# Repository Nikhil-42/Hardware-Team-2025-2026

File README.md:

# Hardware Team 2025-2026
This is the repository for the 2025-2026 IEEE Hardware Team SouthConn for UF.

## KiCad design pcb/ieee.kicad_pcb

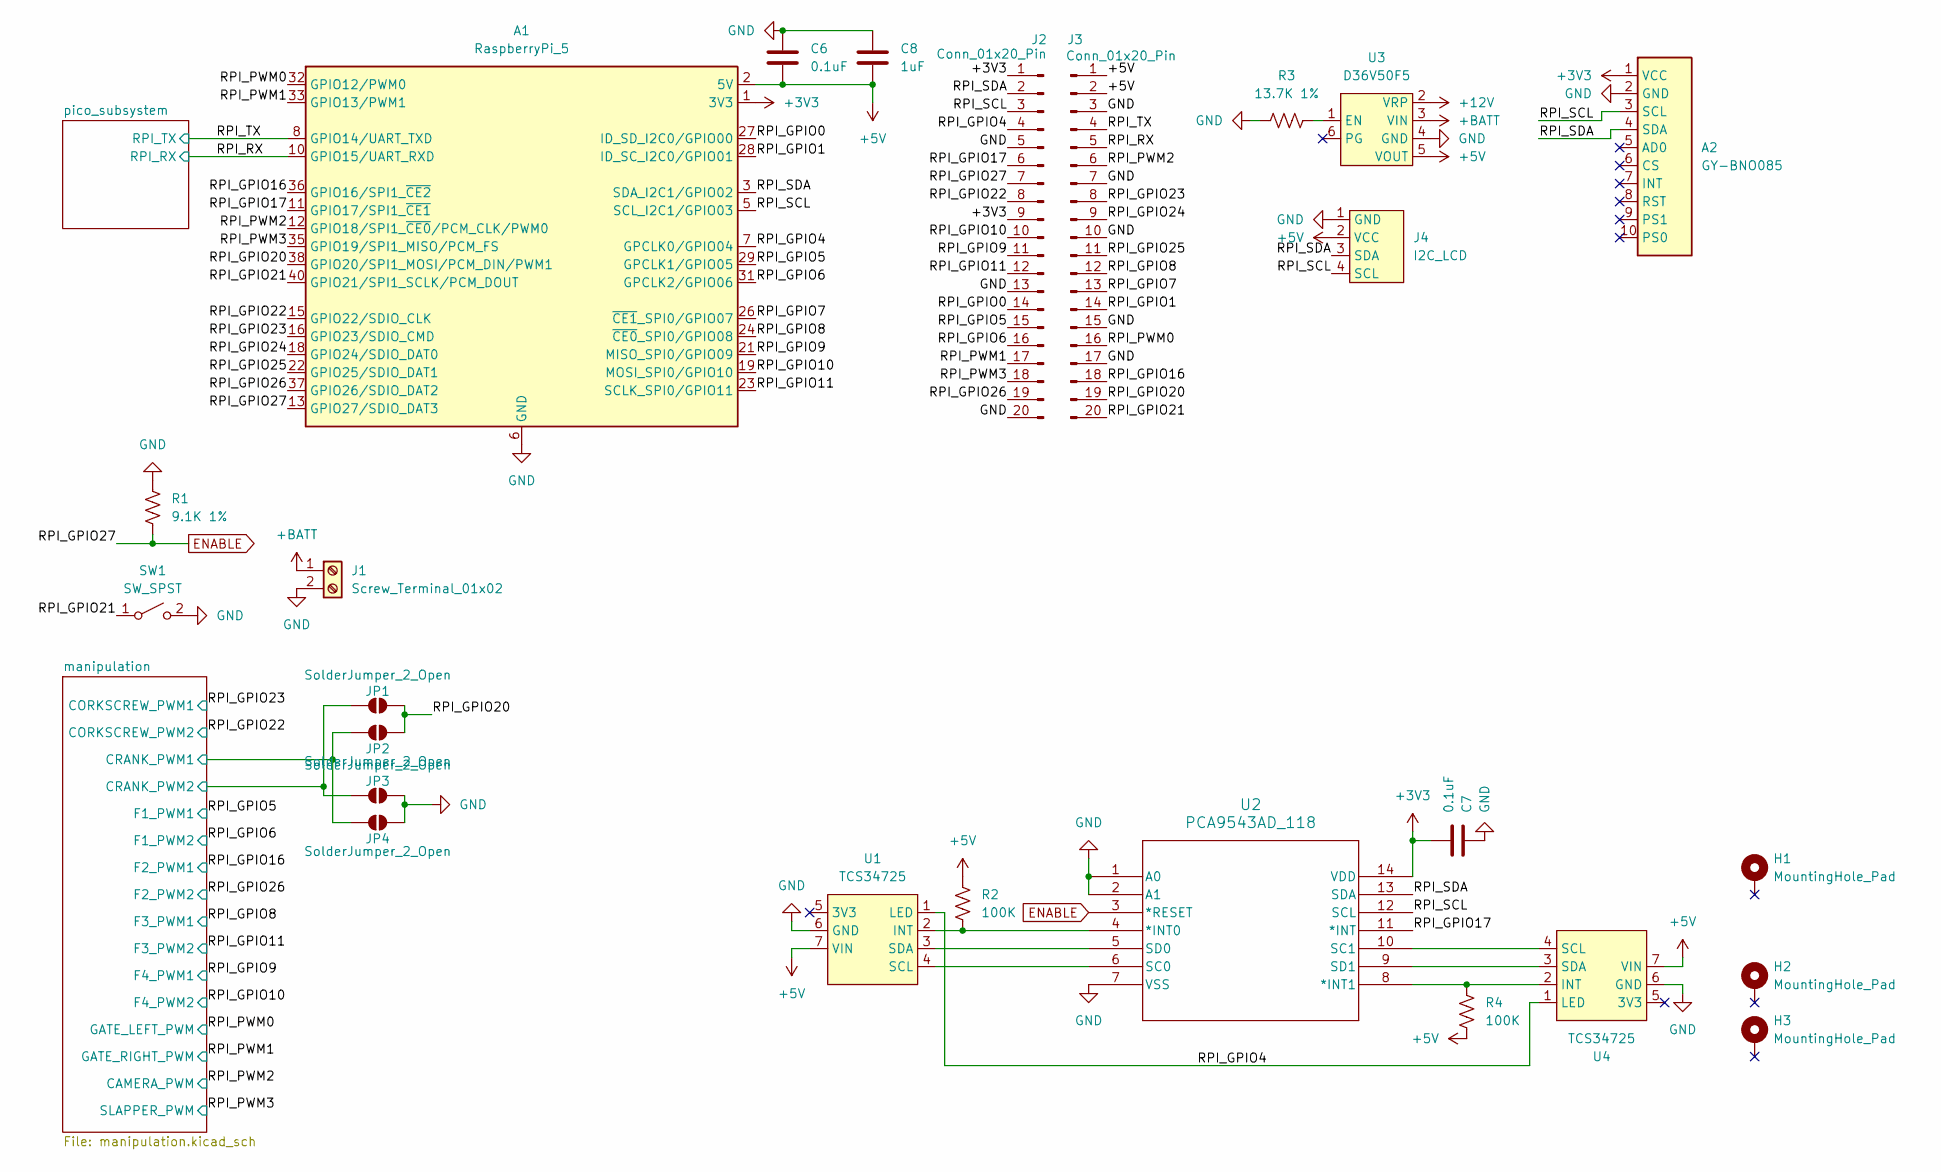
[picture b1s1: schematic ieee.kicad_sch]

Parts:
A1: RaspberryPi_5; Raspberry_Pi_5
A2: GY-BNO085
C6, C7: 0.1uF; C_0603_1608Metric_Pad1.08x0.95mm_HandSolder
C8: 1uF; C_0603_1608Metric_Pad1.08x0.95mm_HandSolder
H1, H2, H3: MountingHole_Pad; MountingHole_3.2mm_M3_Pad
J1: Screw_Terminal_01x02; TerminalBlock_MetzConnect_Type101_RT01602HBWC_1x02_P5.08mm_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
J2, J3: Conn_01x20_Pin; PinHeader_1x20_P2.54mm_Vertical
J4: I2C_LCD; PinHeader_1x04_P2.54mm_Vertical
JP1, JP2, JP3, JP4: SolderJumper_2_Open; SolderJumper-2_P1.3mm_Open_TrianglePad1.0x1.5mm
R1: 9.1K 1%; R_Axial_DIN0309_L9.0mm_D3.2mm_P15.24mm_Horizontal
R2, R4: 100K; R_Axial_DIN0309_L9.0mm_D3.2mm_P15.24mm_Horizontal
R3: 13.7K 1%; R_Axial_DIN0309_L9.0mm_D3.2mm_P15.24mm_Horizontal
SW1: SW_SPST; SW_PUSH_6mm
U1, U4: TCS34725; PinHeader_1x07_P2.54mm_Vertical
U2: PCA9543AD_118; SOIC-14_3.9x8.7mm_P1.27mm
U3: D36V50F5

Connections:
+3V3: A1.1 (3V3), A1.17 (3V3), A2.1 (VCC), C7.2, J2.1, J2.9, U2.14 (VDD)
+5V: A1.2 (5V), A1.4 (5V), C6.2, C8.2, J3.1, J3.2, J4.2 (VCC), R2.1, R4.2, U1.7 (VIN), U3.5 (VOUT), U4.7 (VIN); also elsewhere on the board
+12V: U3.2 (VRP)
+BATT: J1.1 (+), U3.3 (VIN); also elsewhere on the board
/RPI_GPIO0: A1.27 (ID_SD_I2C0/GPIO00), J2.14
/RPI_GPIO1: A1.28 (ID_SC_I2C0/GPIO01), J3.14
/RPI_GPIO4: A1.7 (GPCLK0/GPIO04), J2.4, U1.1 (LED), U4.1 (LED)
/RPI_GPIO5: A1.29 (GPCLK1/GPIO05), J2.15; also elsewhere on the board
/RPI_GPIO6: A1.31 (GPCLK2/GPIO06), J2.16; also elsewhere on the board
/RPI_GPIO7: A1.26 (~CE1_SPI0/GPIO07), J3.13
/RPI_GPIO8: A1.24 (~CE0_SPI0/GPIO08), J3.12; also elsewhere on the board
/RPI_GPIO9: A1.21 (MISO_SPI0/GPIO09), J2.11; also elsewhere on the board
/RPI_GPIO10: A1.19 (MOSI_SPI0/GPIO10), J2.10; also elsewhere on the board
/RPI_GPIO11: A1.23 (SCLK_SPI0/GPIO11), J2.12; also elsewhere on the board
/RPI_GPIO16: A1.36 (GPIO16/SPI1_~CE2), J3.18; also elsewhere on the board
/RPI_GPIO17: A1.11 (GPIO17/SPI1_~CE1), J2.6, U2.11 (*INT)
/RPI_GPIO20: A1.38 (GPIO20/SPI1_MOSI/PCM_DIN/PWM1), J3.19, JP1.2 (B), JP2.2 (B)
/RPI_GPIO21: A1.40 (GPIO21/SPI1_SCLK/PCM_DOUT), J3.20, SW1.1 (A)
/RPI_GPIO22: A1.15 (GPIO22/SDIO_CLK), J2.8; also elsewhere on the board
/RPI_GPIO23: A1.16 (GPIO23/SDIO_CMD), J3.8; also elsewhere on the board
/RPI_GPIO24: A1.18 (GPIO24/SDIO_DAT0), J3.9
/RPI_GPIO25: A1.22 (GPIO25/SDIO_DAT1), J3.11
/RPI_GPIO26: A1.37 (GPIO26/SDIO_DAT2), J2.19; also elsewhere on the board
/RPI_PWM0: A1.32 (GPIO12/PWM0), J3.16; also elsewhere on the board
/RPI_PWM1: A1.33 (GPIO13/PWM1), J2.17; also elsewhere on the board
/RPI_PWM2: A1.12 (GPIO18/SPI1_~CE0/PCM_CLK/PWM0), J3.6; also elsewhere on the board
/RPI_PWM3: A1.35 (GPIO19/SPI1_MISO/PCM_FS), J2.18; also elsewhere on the board
/RPI_RX: A1.10 (GPIO15/UART_RXD), J3.5; also elsewhere on the board
/RPI_SCL: A1.5 (SCL_I2C1/GPIO03), A2.3 (SCL), J2.3, J4.4 (SCL), U2.12 (SCL)
/RPI_SDA: A1.3 (SDA_I2C1/GPIO02), A2.4 (SDA), J2.2, J4.3 (SDA), U2.13 (SDA)
/RPI_TX: A1.8 (GPIO14/UART_TXD), J3.4; also elsewhere on the board
/manipulation/CRANK_PWM1: JP2.1 (A), JP4.1 (A); also elsewhere on the board
/manipulation/CRANK_PWM2: JP1.1 (A), JP3.1 (A); also elsewhere on the board
ENABLE: A1.13 (GPIO27/SDIO_DAT3), J2.7, R1.1, U2.3 (*RESET); also elsewhere on the board
GND: A1.6 (GND), A1.9 (GND), A1.14 (GND), A1.20 (GND), A1.25 (GND), A1.30 (GND), A1.34 (GND), A1.39 (GND), A2.2 (GND), C6.1, C7.1, C8.1, J1.2 (-), J2.5, J2.13, J2.20, J3.3, J3.7, J3.10, J3.15, J3.17, J4.1 (GND), JP3.2 (B), JP4.2 (B), R1.2, R3.1, SW1.2 (B), U1.6 (GND), U2.1 (A0), U2.2 (A1), U2.7 (VSS), U3.4 (GND), U4.6 (GND); also elsewhere on the board
unnamed: R2.2, U1.2 (INT), U2.4 (*INT0)
unnamed: U1.4 (SCL), U2.6 (SC0)
unnamed: U1.3 (SDA), U2.5 (SD0)
unnamed: R4.1, U2.8 (*INT1), U4.2 (INT)
unnamed: U2.10 (SC1), U4.4 (SCL)
unnamed: U2.9 (SD1), U4.3 (SDA)
unnamed: R3.2, U3.1 (EN)

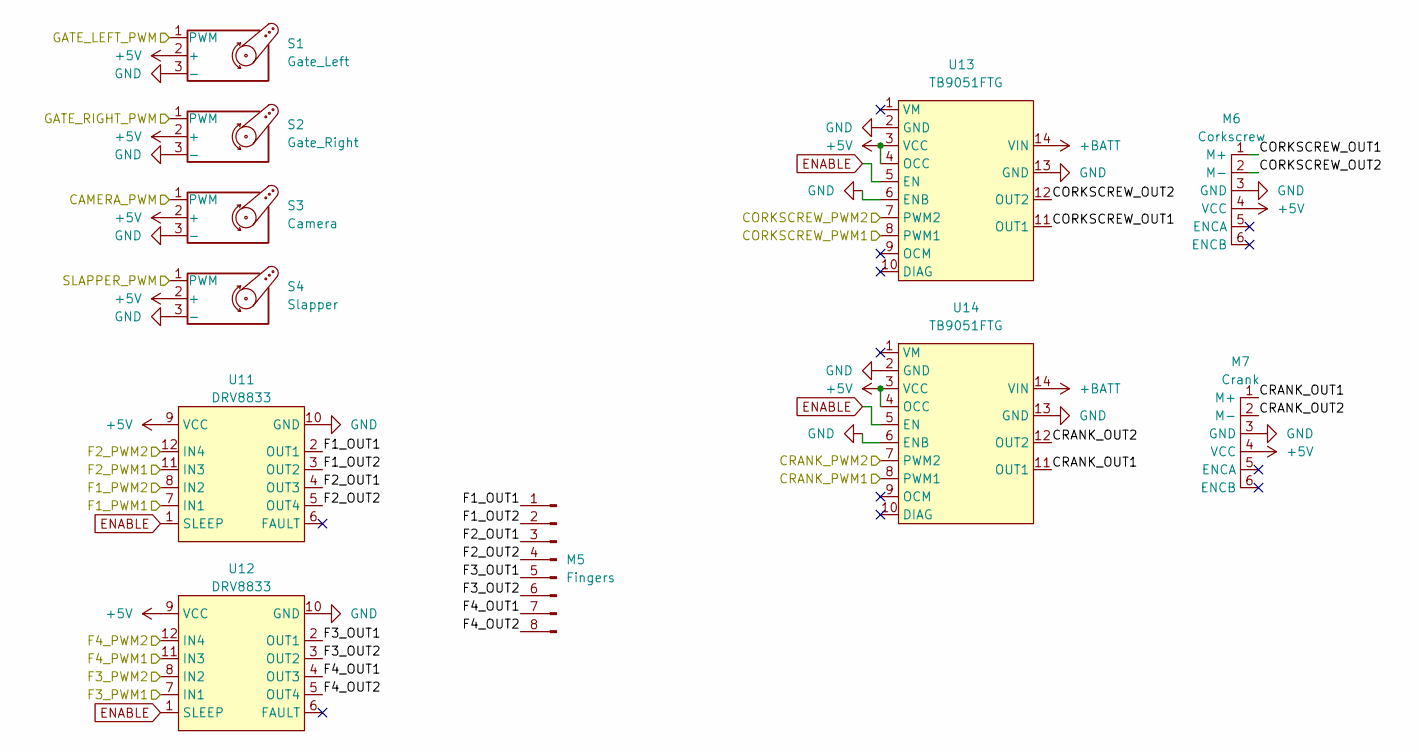
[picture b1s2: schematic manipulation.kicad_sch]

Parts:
M5: Fingers; PinHeader_1x08_P2.54mm_Vertical
M6: Corkscrew; PinHeader_1x06_P2.54mm_Vertical
M7: Crank; PinHeader_1x06_P2.54mm_Vertical
S1: Gate_Left; PinHeader_1x03_P2.54mm_Vertical
S2: Gate_Right; PinHeader_1x03_P2.54mm_Vertical
S3: Camera; PinHeader_1x03_P2.54mm_Vertical
S4: Slapper; PinHeader_1x03_P2.54mm_Vertical
U11, U12: DRV8833
U13, U14: TB9051FTG

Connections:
+5V: M6.4 (VCC), M7.4 (VCC), S1.2 (+), S2.2 (+), S3.2 (+), S4.2 (+), U11.9 (VCC), U12.9 (VCC), U13.3 (VCC), U13.4 (OCC), U14.3 (VCC), U14.4 (OCC); also elsewhere on the board
+BATT: U13.14 (VIN), U14.14 (VIN); also elsewhere on the board
/RPI_GPIO5: U11.7 (IN1); also elsewhere on the board
/RPI_GPIO6: U11.8 (IN2); also elsewhere on the board
/RPI_GPIO8: U12.7 (IN1); also elsewhere on the board
/RPI_GPIO9: U12.11 (IN3); also elsewhere on the board
/RPI_GPIO10: U12.12 (IN4); also elsewhere on the board
/RPI_GPIO11: U12.8 (IN2); also elsewhere on the board
/RPI_GPIO16: U11.11 (IN3); also elsewhere on the board
/RPI_GPIO22: U13.7 (PWM2); also elsewhere on the board
/RPI_GPIO23: U13.8 (PWM1); also elsewhere on the board
/RPI_GPIO26: U11.12 (IN4); also elsewhere on the board
/RPI_PWM0: S1.1 (PWM); also elsewhere on the board
/RPI_PWM1: S2.1 (PWM); also elsewhere on the board
/RPI_PWM2: S3.1 (PWM); also elsewhere on the board
/RPI_PWM3: S4.1 (PWM); also elsewhere on the board
/manipulation/CORKSCREW_OUT1: M6.1 (M+), U13.11 (OUT1)
/manipulation/CORKSCREW_OUT2: M6.2 (M-), U13.12 (OUT2)
/manipulation/CRANK_OUT1: M7.1 (M+), U14.11 (OUT1)
/manipulation/CRANK_OUT2: M7.2 (M-), U14.12 (OUT2)
/manipulation/CRANK_PWM1: U14.8 (PWM1); also elsewhere on the board
/manipulation/CRANK_PWM2: U14.7 (PWM2); also elsewhere on the board
/manipulation/F1_OUT1: M5.1, U11.2 (OUT1)
/manipulation/F1_OUT2: M5.2, U11.3 (OUT2)
/manipulation/F2_OUT1: M5.3, U11.4 (OUT3)
/manipulation/F2_OUT2: M5.4, U11.5 (OUT4)
/manipulation/F3_OUT1: M5.5, U12.2 (OUT1)
/manipulation/F3_OUT2: M5.6, U12.3 (OUT2)
/manipulation/F4_OUT1: M5.7, U12.4 (OUT3)
/manipulation/F4_OUT2: M5.8, U12.5 (OUT4)
ENABLE: U11.1 (SLEEP), U12.1 (SLEEP), U13.5 (EN), U14.5 (EN); also elsewhere on the board
GND: M6.3 (GND), M7.3 (GND), S1.3 (-), S2.3 (-), S3.3 (-), S4.3 (-), U11.10 (GND), U12.10 (GND), U13.2 (GND), U13.6 (ENB), U13.13 (GND), U14.2 (GND), U14.6 (ENB), U14.13 (GND); also elsewhere on the board

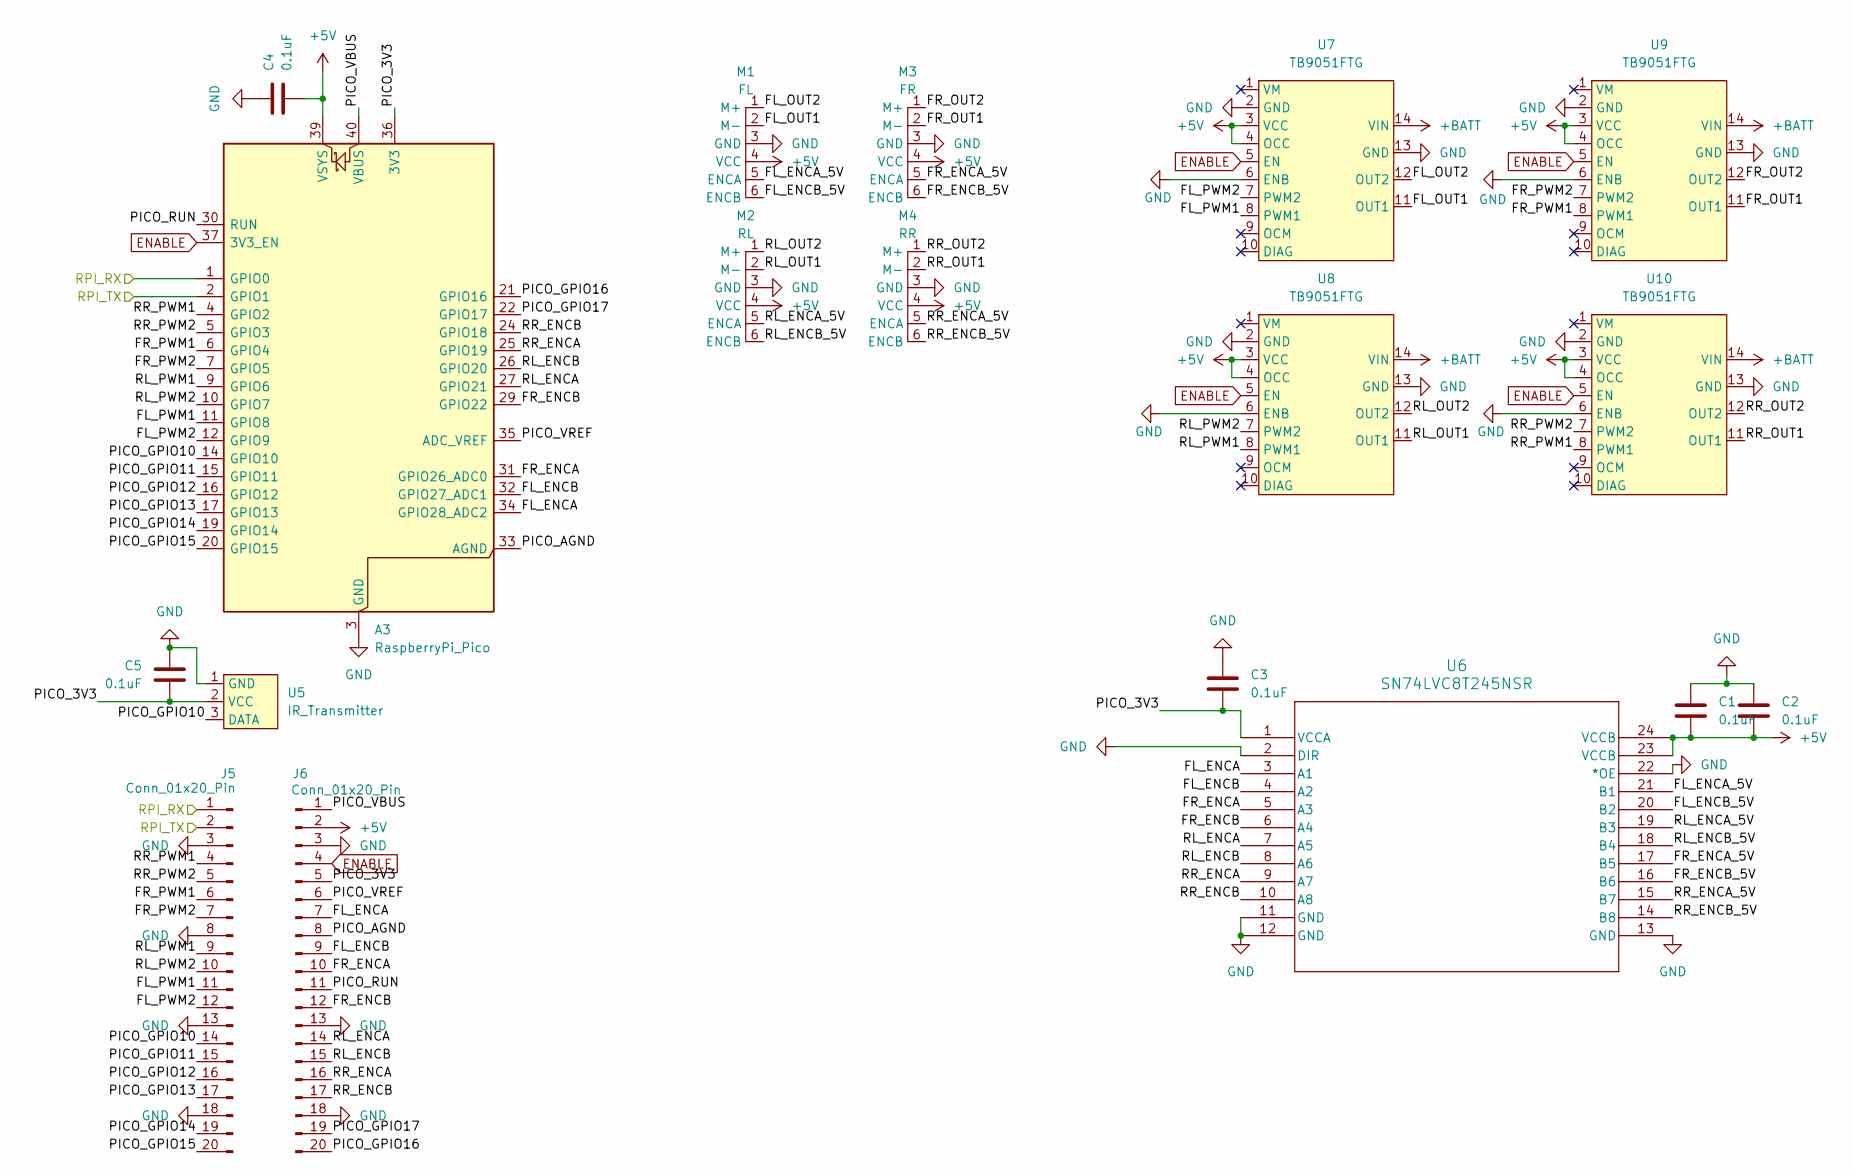
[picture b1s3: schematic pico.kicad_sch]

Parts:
A3: RaspberryPi_Pico; RaspberryPi_Pico_Common_Unspecified
C1, C2, C3, C4, C5: 0.1uF; C_0603_1608Metric_Pad1.08x0.95mm_HandSolder
J5, J6: Conn_01x20_Pin; PinHeader_1x20_P2.54mm_Vertical
M1: FL; PinHeader_1x06_P2.54mm_Vertical
M2: RL; PinHeader_1x06_P2.54mm_Vertical
M3: FR; PinHeader_1x06_P2.54mm_Vertical
M4: RR; PinHeader_1x06_P2.54mm_Vertical
U5: IR_Transmitter; PinHeader_1x03_P2.54mm_Vertical
U6: SN74LVC8T245NSR; NS24
U7, U8, U9, U10: TB9051FTG

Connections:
+5V: A3.39 (VSYS), C1.2, C2.2, C4.2, J6.2, M1.4 (VCC), M2.4 (VCC), M3.4 (VCC), M4.4 (VCC), U6.23 (VCCB), U6.24 (VCCB), U7.3 (VCC), U7.4 (OCC), U8.3 (VCC), U8.4 (OCC), U9.3 (VCC), U9.4 (OCC), U10.3 (VCC), U10.4 (OCC); also elsewhere on the board
+BATT: U7.14 (VIN), U8.14 (VIN), U9.14 (VIN), U10.14 (VIN); also elsewhere on the board
/RPI_RX: A3.1 (GPIO0), J5.1; also elsewhere on the board
/RPI_TX: A3.2 (GPIO1), J5.2; also elsewhere on the board
/pico_subsystem/FL_ENCA: A3.34 (GPIO28_ADC2), J6.7, U6.3 (A1)
/pico_subsystem/FL_ENCA_5V: M1.5 (ENCA), U6.21 (B1)
/pico_subsystem/FL_ENCB: A3.32 (GPIO27_ADC1), J6.9, U6.4 (A2)
/pico_subsystem/FL_ENCB_5V: M1.6 (ENCB), U6.20 (B2)
/pico_subsystem/FL_OUT1: M1.2 (M-), U7.11 (OUT1)
/pico_subsystem/FL_OUT2: M1.1 (M+), U7.12 (OUT2)
/pico_subsystem/FL_PWM1: A3.11 (GPIO8), J5.11, U7.8 (PWM1)
/pico_subsystem/FL_PWM2: A3.12 (GPIO9), J5.12, U7.7 (PWM2)
/pico_subsystem/FR_ENCA: A3.31 (GPIO26_ADC0), J6.10, U6.5 (A3)
/pico_subsystem/FR_ENCA_5V: M3.5 (ENCA), U6.17 (B5)
/pico_subsystem/FR_ENCB: A3.29 (GPIO22), J6.12, U6.6 (A4)
/pico_subsystem/FR_ENCB_5V: M3.6 (ENCB), U6.16 (B6)
/pico_subsystem/FR_OUT1: M3.2 (M-), U9.11 (OUT1)
/pico_subsystem/FR_OUT2: M3.1 (M+), U9.12 (OUT2)
/pico_subsystem/FR_PWM1: A3.6 (GPIO4), J5.6, U9.8 (PWM1)
/pico_subsystem/FR_PWM2: A3.7 (GPIO5), J5.7, U9.7 (PWM2)
/pico_subsystem/PICO_3V3: A3.36 (3V3), C3.2, C5.2, J6.5, U5.2 (VCC), U6.1 (VCCA)
/pico_subsystem/PICO_AGND: A3.33 (AGND), J6.8
/pico_subsystem/PICO_GPIO10: A3.14 (GPIO10), J5.14, U5.3 (DATA)
/pico_subsystem/PICO_GPIO11: A3.15 (GPIO11), J5.15
/pico_subsystem/PICO_GPIO12: A3.16 (GPIO12), J5.16
/pico_subsystem/PICO_GPIO13: A3.17 (GPIO13), J5.17
/pico_subsystem/PICO_GPIO14: A3.19 (GPIO14), J5.19
/pico_subsystem/PICO_GPIO15: A3.20 (GPIO15), J5.20
/pico_subsystem/PICO_GPIO16: A3.21 (GPIO16), J6.20
/pico_subsystem/PICO_GPIO17: A3.22 (GPIO17), J6.19
/pico_subsystem/PICO_RUN: A3.30 (RUN), J6.11
/pico_subsystem/PICO_VBUS: A3.40 (VBUS), J6.1
/pico_subsystem/PICO_VREF: A3.35 (ADC_VREF), J6.6
/pico_subsystem/RL_ENCA: A3.27 (GPIO21), J6.14, U6.7 (A5)
/pico_subsystem/RL_ENCA_5V: M2.5 (ENCA), U6.19 (B3)
/pico_subsystem/RL_ENCB: A3.26 (GPIO20), J6.15, U6.8 (A6)
/pico_subsystem/RL_ENCB_5V: M2.6 (ENCB), U6.18 (B4)
/pico_subsystem/RL_OUT1: M2.2 (M-), U8.11 (OUT1)
/pico_subsystem/RL_OUT2: M2.1 (M+), U8.12 (OUT2)
/pico_subsystem/RL_PWM1: A3.9 (GPIO6), J5.9, U8.8 (PWM1)
/pico_subsystem/RL_PWM2: A3.10 (GPIO7), J5.10, U8.7 (PWM2)
/pico_subsystem/RR_ENCA: A3.25 (GPIO19), J6.16, U6.9 (A7)
/pico_subsystem/RR_ENCA_5V: M4.5 (ENCA), U6.15 (B7)
/pico_subsystem/RR_ENCB: A3.24 (GPIO18), J6.17, U6.10 (A8)
/pico_subsystem/RR_ENCB_5V: M4.6 (ENCB), U6.14 (B8)
/pico_subsystem/RR_OUT1: M4.2 (M-), U10.11 (OUT1)
/pico_subsystem/RR_OUT2: M4.1 (M+), U10.12 (OUT2)
/pico_subsystem/RR_PWM1: A3.4 (GPIO2), J5.4, U10.8 (PWM1)
/pico_subsystem/RR_PWM2: A3.5 (GPIO3), J5.5, U10.7 (PWM2)
ENABLE: A3.37 (3V3_EN), J6.4, U7.5 (EN), U8.5 (EN), U9.5 (EN), U10.5 (EN); also elsewhere on the board
GND: A3.3 (GND), A3.8 (GND), A3.13 (GND), A3.18 (GND), A3.23 (GND), A3.28 (GND), A3.38 (GND), C1.1, C2.1, C3.1, C4.1, C5.1, J5.3, J5.8, J5.13, J5.18, J6.3, J6.13, J6.18, M1.3 (GND), M2.3 (GND), M3.3 (GND), M4.3 (GND), U5.1 (GND), U6.2 (DIR), U6.11 (GND), U6.12 (GND), U6.13 (GND), U6.22 (*OE), U7.2 (GND), U7.6 (ENB), U7.13 (GND), U8.2 (GND), U8.6 (ENB), U8.13 (GND), U9.2 (GND), U9.6 (ENB), U9.13 (GND), U10.2 (GND), U10.6 (ENB), U10.13 (GND); also elsewhere on the board

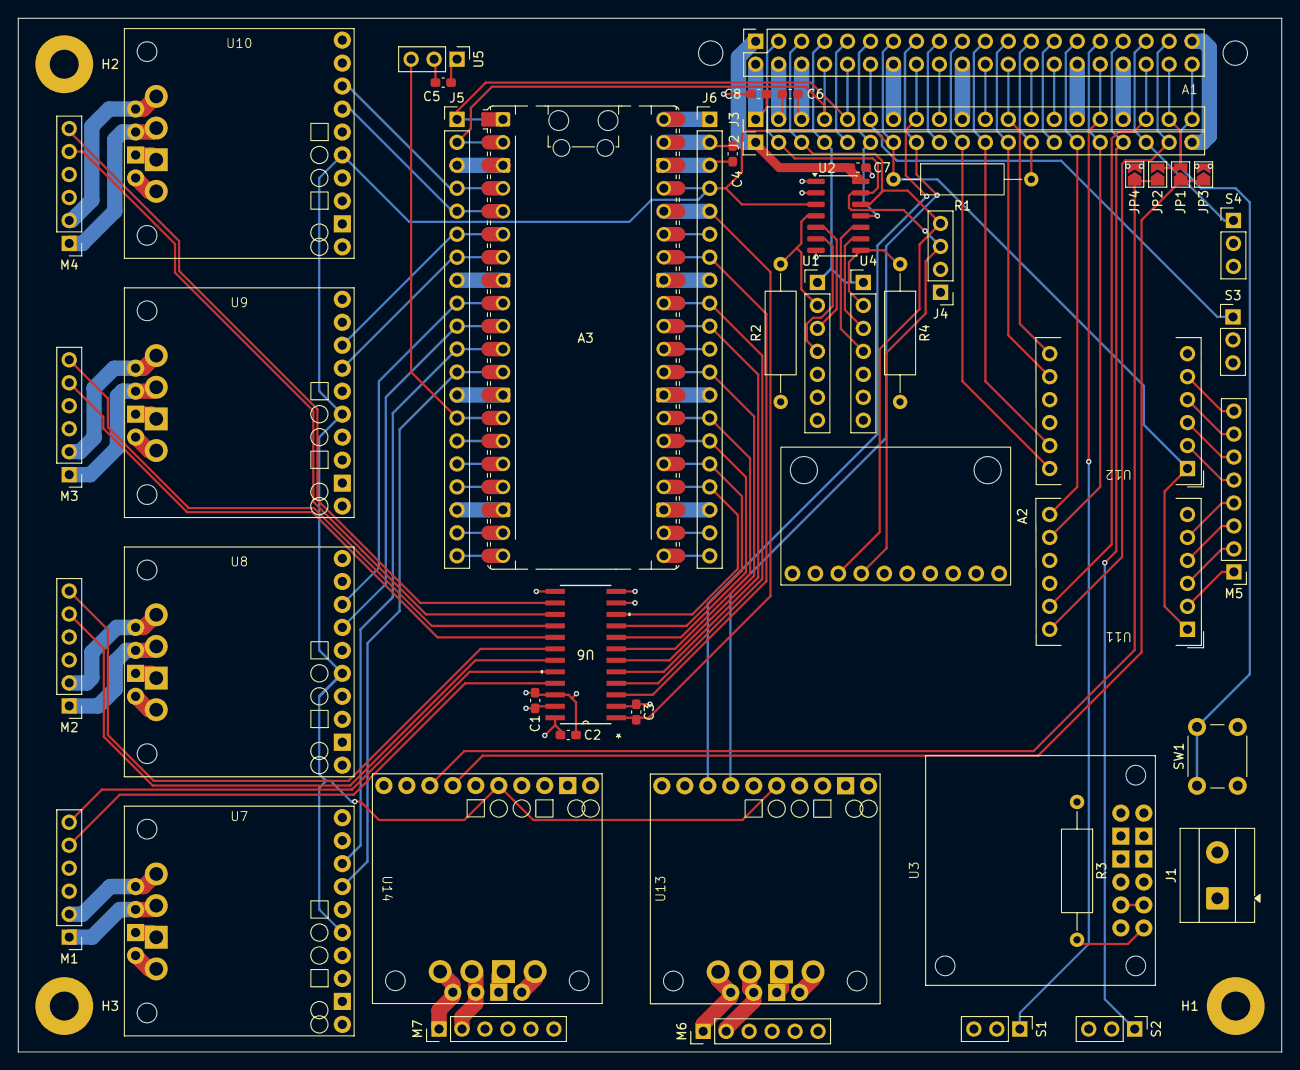
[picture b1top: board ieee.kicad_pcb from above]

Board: 4 copper layers, 139.7 x 114.3 mm, 54 parts (0 on the bottom side), 98 nets.

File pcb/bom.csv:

"Id";"Designator";"Footprint";"Quantity";"Designation";"Supplier and ref";
1;"U6";"NS24";1;"SN74LVC8T245NSR";;;
2;"C3,C1,C4,C7,C2,C5,C6";"C_0603_1608Metric_Pad1.08x0.95mm_HandSolder";7;"0.1uF";;;
3;"U5";"PinHeader_1x03_P2.54mm_Vertical";1;"IR_Transmitter";;;
4;"U2";"SOIC-14_3.9x8.7mm_P1.27mm";1;"PCA9543AD_118";;;
5;"M1";"PinHeader_1x06_P2.54mm_Vertical";1;"FL";;;
6;"U4,U1";"PinHeader_1x07_P2.54mm_Vertical";2;"TCS34725";;;
7;"S1";"PinHeader_1x03_P2.54mm_Vertical";1;"Gate_Left";;;
8;"J1";"TerminalBlock_MetzConnect_Type101_RT01602HBWC_1x02_P5.08mm_Horizontal";1;"Screw_Terminal_01x02";;;
9;"M3";"PinHeader_1x06_P2.54mm_Vertical";1;"FR";;;
10;"U13,U10,U8,U7,U9,U14";"TB9051FTG";6;"TB9051FTG";;;
11;"J3,J6,J2,J5";"PinHeader_1x20_P2.54mm_Vertical";4;"Conn_01x20_Pin";;;
12;"S3";"PinHeader_1x03_P2.54mm_Vertical";1;"Camera";;;
13;"M2";"PinHeader_1x06_P2.54mm_Vertical";1;"RL";;;
14;"A3";"RaspberryPi_Pico_Common_Unspecified";1;"RaspberryPi_Pico";;;
15;"U12,U11";"DRV8833";2;"DRV8833";;;
16;"SW1";"SW_PUSH_6mm";1;"SW_SPST";;;
17;"R3";"R_Axial_DIN0309_L9.0mm_D3.2mm_P15.24mm_Horizontal";1;"13.7K 1%";;;
18;"J4";"PinHeader_1x04_P2.54mm_Vertical";1;"I2C_LCD";;;
19;"R1";"R_Axial_DIN0309_L9.0mm_D3.2mm_P15.24mm_Horizontal";1;"9.1K 1%";;;
20;"M6";"PinHeader_1x06_P2.54mm_Vertical";1;"Corkscrew";;;
21;"A1";"Raspberry_Pi_5";1;"RaspberryPi_5";;;
22;"M5";"PinHeader_1x08_P2.54mm_Vertical";1;"Fingers";;;
23;"S4";"PinHeader_1x03_P2.54mm_Vertical";1;"Slapper";;;
24;"U3";"D36V50F5";1;"D36V50F5";;;
25;"A2";"GY-BNO085";1;"GY-BNO085";;;
26;"R2,R4";"R_Axial_DIN0309_L9.0mm_D3.2mm_P15.24mm_Horizontal";2;"100K";;;
27;"M7";"PinHeader_1x06_P2.54mm_Vertical";1;"Crank";;;
28;"S2";"PinHeader_1x03_P2.54mm_Vertical";1;"Gate_Right";;;
29;"M4";"PinHeader_1x06_P2.54mm_Vertical";1;"RR";;;
30;"C8";"C_0603_1608Metric_Pad1.08x0.95mm_HandSolder";1;"1uF";;;

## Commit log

2026-01-13 motor control and transmitter code
    Code for motor control and IR transmitter
2026-01-15 Add Rpi doc
2026-01-15 most recent code
    need to finish odom and update uart communication
2026-01-22 updated code
    updated and working code for motor control. For fixed sampling, calculated distance between ticks of encoder channels instead of cumulative counts which improved RPM calculations significantly.
2026-01-27 Push past changes
    Push to update repo with changes made a few days ago.
2026-02-03 Fix cmd_vel receipt
2026-02-03 Add gitignore to hub
2026-02-03 Create ROS2 package
2026-02-03 Publishing odom (no covar)
2026-02-03 Updates to pico code
2026-02-06 updating repo
2026-02-06 Add bno085-ros2-driver
2026-02-06 Add support for fingers via finger service
2026-02-06 measurement updates
    updated robot geometry measurements for kinematics and odom
2026-02-10 set up action node using nav2's navigate to pose
2026-02-10 attempt to run an action node for navigating to a pose using nav2, behavior tree and ros2
2026-02-12 Create PCB
2026-02-13 Fix ERC issues and layout connectors
2026-02-13 Save after closing KiCAD
2026-02-13 Start routing
2026-02-13 Remove edge cuts from IMU
2026-02-15 Route RPI and Pico breakouts
2026-02-15 Route I2C and planes
2026-02-15 project files
2026-02-16 Finish layout
2026-02-16 Fix after design review
2026-02-16 Fab outputs
2026-02-17 To run the bt should hopefully just need ros2 launch nav2_bringup navigation_launch.py and ros2 run bt_navigation bt_navigator_node
2026-02-17 hopefully runnable behavior tree for navigating to a set pose using nav2 NavigateToPose and BehaviorTreeCPP. See readme.txt in package folder for information on running the package.
2026-02-17 Add camera_ros as submodule
2026-02-19 Create robot_bringup launch file
2026-02-21 Added action server and PID controller. Need to write action client to complete DriveToPose
2026-02-21 more work on drive to pose
2026-02-22 working action server, need to finish dependencies on client side
2026-02-22 finished the drive to pose action client-server and can see it publishing cmd_vel but robot doesn't actually move :(
2026-02-23 updating full package stack. Drive to pose still not fully functional so I'll have to look through the code again.
2026-02-25 ran some test pose cases to debug the issue in the code. Saved some ros bags to look over
2026-02-26 changes to robot geometry and encoder difference calculation
2026-02-27 added xor checksum to remove possible corrupted frames and some failed turtlesim action attempts
2026-02-27 latest camera and drive to pose changes
2026-02-27 updated PID controller with additional control logic and transformed errors from odom to baselink frame
2026-02-28 most recent changes
2026-02-28 Add BehaviorTree.ROS2 as a submodule
2026-02-28 Consolidate packages and fix start_light_node
2026-02-28 Create behaviors package from sample
2026-02-28 Add custom nodes to behaviors
2026-02-28 Keyboard and button full auto
2026-03-03 Implement WaitForStart, ReportColor, DriveWitVel
2026-03-04 finished drive with vel
2026-03-04 updated pico code
2026-03-04 Add ReportColor to behavior tree
2026-03-04 Repeat NEC send pico
2026-03-04 Switch to PIO based NEC (from Adafruit)
2026-03-05 Speed up broadcast interval
2026-03-10 Update Pico code for PCB layout
2026-03-12 most updated code
2026-03-14 updated pico pinout and attempted fixes for motor control
2026-03-14 enable picoboot via uart
2026-03-14 Fix motor action server
2026-03-14 map->base_link transformation, imu in ekf, covariances added. Need to build in this branch on Pi to resolve remaining errors
2026-03-14 Add the motor control nodes
2026-03-14 Add picoboot3
2026-03-14 WIP base to map
2026-03-14 update behavior trees
2026-03-14 Functioning autonomous!
2026-03-14 Button autonomous completed
